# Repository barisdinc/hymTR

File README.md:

# hymTR
APRS Tracker
Arduino Uno ile calisan bir APRS tracker projesidir. 
Temel oalrak asagidaki ozelliklere sahiptir :
- Herhangibir arduino ile calisir
- Telsize hoparlor arayuzunden baglanir
- 4 bitlik bir Direnc iskelesi (resistor ladder) DAC ile calisir (16 seviye)
- Asagidaki verileri GPS den okur
  - Zaman
  - Pozisyon
  - Hiz/yonlenme vb
  - Uydu sayisi
  - Fix durumu
- Smart beacon ozelligi ile hiz ile orantili olarak gonderme sikligini degistirir
- Verileri EEPROM'da saklar
- PC Yazilimi ile tum ayarlari degistirilebilir

Eklenmesi planlanan ozellikler :
- APRS dinleme ozelligi
- Dorji radyolari yonetebilme ozelligi
- Display ekelenebilir

PC Yonetim arayuzu programi "hymTR Ayar Programi" ayri bir repository icindedir.

Donanim detaylari icin <A HREF="https://github.com/barisdinc/hymTR/blob/master/Hardware/README.md">Donanim Sayfasi'na bakabilirsiniz</A>

Ocak 2020

Proje destekcileri :
--------------------
- TA2GY Cem Karagoz
- TA6AEU Emre Keles

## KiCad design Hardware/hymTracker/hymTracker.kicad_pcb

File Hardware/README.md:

hymTRacker Donanim Genel gorunumu

<IMG SRC=https://github.com/barisdinc/hymTR/blob/master/Hardware/pcb_genel.jpeg>
<IMG SRC=https://github.com/barisdinc/hymTR/blob/master/Hardware/pcb_3d_ustten.jpeg>
<IMG SRC=https://github.com/barisdinc/hymTR/blob/master/Hardware/pcb_3d_acili.jpeg>
<IMG SRC=https://github.com/barisdinc/hymTR/blob/master/Hardware/pcb_3d_alttan.jpeg>
<IMG SRC=https://github.com/barisdinc/hymTR/blob/master/Hardware/resim1.jpeg>
<IMG SRC=https://github.com/barisdinc/hymTR/blob/master/Hardware/resim2.jpeg>
<IMG SRC=https://github.com/barisdinc/hymTR/blob/master/Hardware/resim3.jpeg>
<IMG SRC=https://github.com/barisdinc/hymTR/blob/master/Hardware/resim4.jpeg>
<IMG SRC=https://github.com/barisdinc/hymTR/blob/master/Hardware/resim5.jpeg>
<IMG SRC=https://github.com/barisdinc/hymTR/blob/master/Hardware/resim6.jpeg>
<IMG SRC=https://github.com/barisdinc/hymTR/blob/master/Hardware/resim7.jpeg>
<IMG SRC=https://github.com/barisdinc/hymTR/blob/master/Hardware/resim8.jpeg>
<IMG SRC=https://github.com/barisdinc/hymTR/blob/master/Hardware/resim9.jpeg>
<IMG SRC=https://github.com/barisdinc/hymTR/blob/master/Hardware/resim10.jpeg>

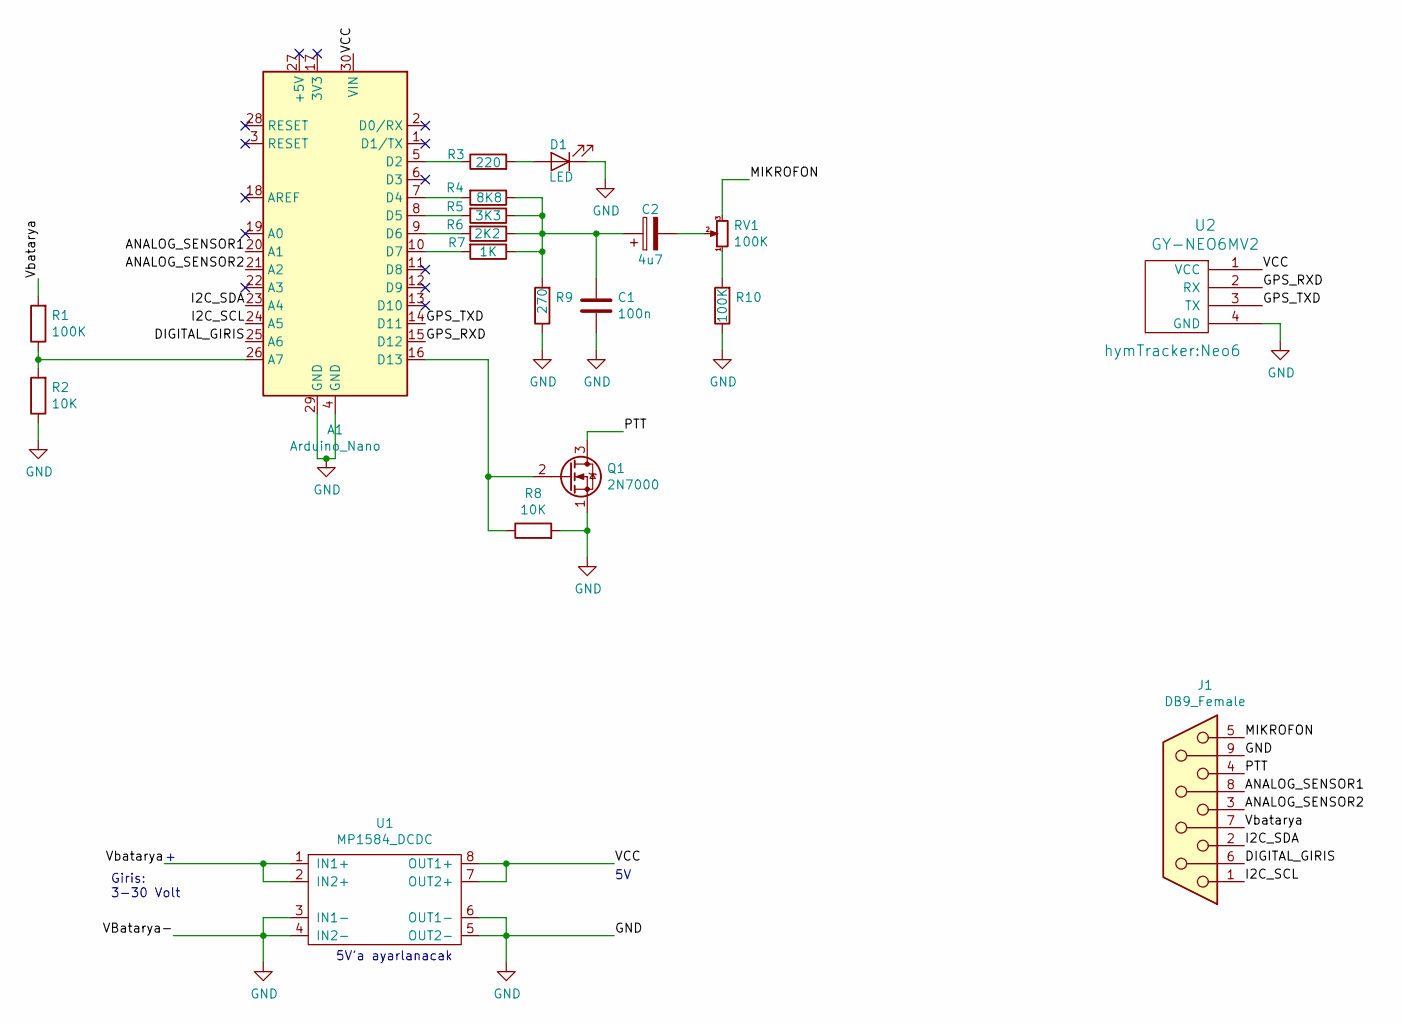
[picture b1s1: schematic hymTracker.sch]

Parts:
A1: Arduino_Nano
C1: 100n; C_0805_2012Metric
C2: 4u7; C_1206_3216Metric
D1: LED; LED_0805_2012Metric
J1: DB9_Female; DSUB-9_Female_Horizontal_P2.77x2.84mm_EdgePinOffset7.70mm_H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
Q1: 2N7000; TO-92_Inline
R1, R10: 100K; R_0805_2012Metric
R2, R8: 10K; R_0805_2012Metric
R3: 220; R_0805_2012Metric
R4: 8K8; R_0805_2012Metric
R5: 3K3; R_0805_2012Metric
R6: 2K2; R_0805_2012Metric
R7: 1K; R_0805_2012Metric
R9: 270; R_0805_2012Metric
RV1: 100K; Potentiometer_ACP_CA9-V10_Vertical_Hole
U1: MP1584_DCDC; MP1854EN_board
U2: GY-NEO6MV2; Neo6

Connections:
/ANALOG_SENSOR1: A1.20 (A1), J1.8
/ANALOG_SENSOR2: A1.21 (A2), J1.3
/DIGITAL_GIRIS: A1.25 (A6), J1.6
/GPS_RXD: A1.15 (D12), U2.2 (RX)
/GPS_TXD: A1.14 (D11), U2.3 (TX)
/I2C_SCL: A1.24 (A5), J1.1
/I2C_SDA: A1.23 (A4), J1.2
/MIKROFON: J1.5, RV1.3
/PTT: J1.4, Q1.3 (D)
/VCC: A1.30 (VIN), U1.7 (OUT2+), U1.8 (OUT1+), U2.1 (VCC)
/Vbatarya: J1.7, R1.2, U1.1 (IN1+), U1.2 (IN2+)
GND: A1.4 (GND), A1.29 (GND), C1.2, D1.1 (K), J1.9, Q1.1 (S), R2.1, R8.2, R9.1, R10.1, U1.3 (IN1-), U1.4 (IN2-), U1.5 (OUT2-), U1.6 (OUT1-), U2.4 (GND)
unnamed: A1.5 (D2), R3.1
unnamed: A1.7 (D4), R4.2
unnamed: A1.8 (D5), R5.2
unnamed: A1.9 (D6), R6.2
unnamed: A1.10 (D7), R7.2
unnamed: A1.16 (D13), Q1.2 (G), R8.1
unnamed: A1.26 (A7), R1.1, R2.2
unnamed: C1.1, C2.1, R4.1, R5.1, R6.1, R7.1, R9.2
unnamed: C2.2, RV1.2
unnamed: D1.2 (A), R3.2
unnamed: R10.2, RV1.1

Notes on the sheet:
5V'a ayarlanacak
Giris: 3-30 Volt

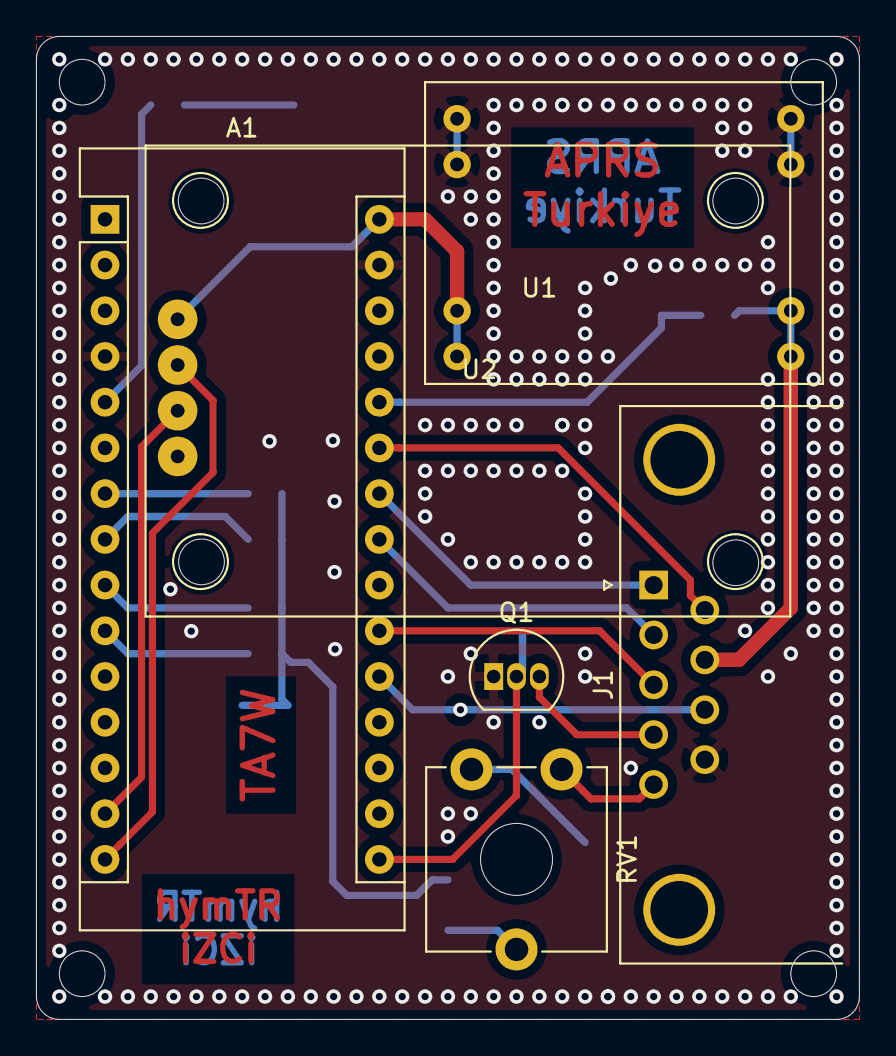
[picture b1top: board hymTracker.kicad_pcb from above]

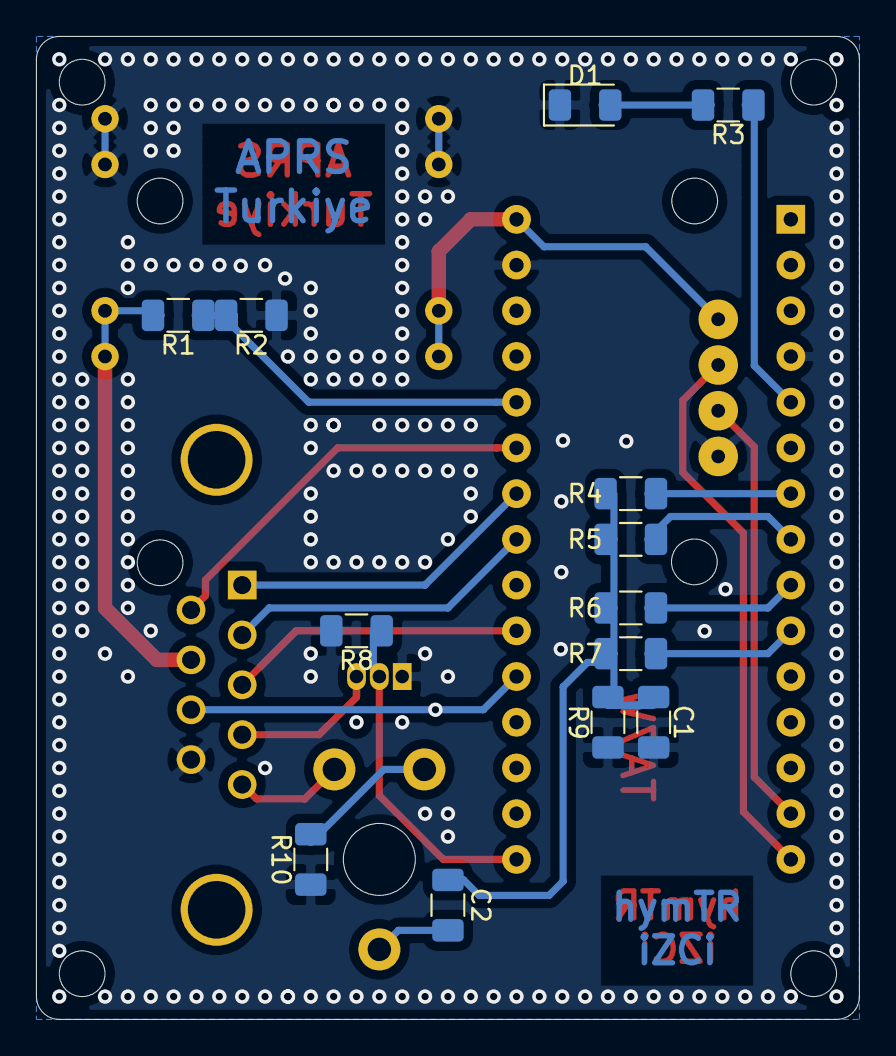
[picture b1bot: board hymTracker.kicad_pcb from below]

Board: 2 copper layers, 45.7 x 54.6 mm, 19 parts (13 on the bottom side), 23 nets.

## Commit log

2020-01-06 ilk baslangic
2020-01-07 initial push
2020-01-10 Seri port atayuzu eklendi.. EEPROM yazma okuma eklendi
2020-01-11 seri port haberlesmesi kabaca tamam
2020-01-11 Adafruit GPS denemesi.. memory yetmiyor
2020-01-18 GPS okuma ve Seri port rutinleri degistirildi
    gps okumak icin nmae NeoGPS kutuphanesine gecildi
    seri port icin neoSWserial kutuphanesi ve interrupt yapisina gecildi
2020-01-18 Seri port yonetim arayuzu
2020-01-19 for backup
2020-01-19 backup 2
2020-01-19 old version
2020-01-19 Derece'den NMEA ya cevirim formulu degistirildi
2020-01-19 aci hesaplari duzeltildi
2020-01-19 altitude feet->metre cevriomi duzeltildi
2020-01-19 modified for new library DIR / SPD/ CSE
2020-01-19 tcommit
2020-01-29 APRS_Destination updated
2020-02-04 last modif for seiral comms
2020-02-05 restructured
2020-02-05 src deleted
2020-02-05 restructure 2
2020-02-05 libraries
2020-02-05 headers
2020-02-05 tests removed
2020-02-05 tested with emre
2020-02-06 sure hatasi
2020-02-09 callsign length problem solved
2020-03-15 Hardware eklendi
2020-03-15 sema cizildi
2020-03-15 pcb ye hazir
2020-03-15 pcb lib
2020-03-16 PCD cizimi tamamlandi
2020-03-16 PCD resimleri
2020-03-16 PCB logo
2020-03-17 yeni 3d elemanlar
2020-03-17 yeni 3d elemanlar 2
2020-03-17 resimler guncellendi
2020-04-17 Panel eklentisi
2020-04-18 panel.. callsign and RULER added
2020-04-18 gerbers created
2020-06-23 basilan
2020-06-23 yedek - kullanma
2020-07-20 re-branding
2020-08-06 dergi yazi (doc)
2020-08-06 dergi yazi (odt)
2020-08-06 dergi yazi (pdf)
2020-08-06 R805->R1206 (small)
2020-08-10 son degisiklikler
2020-08-11 temizlik
2020-08-17 gps ters cevrildi
2020-08-17 gerber output
2020-09-03 dual version
2020-10-02 Destination APIzci duzeltmesi yapildi
2020-10-02 GPS Default var yapildi
2020-10-02 D3 moved to D13 for TX
2020-10-07 cse/head phg corrected
2020-12-21 APRS sembolu gondermeme hatasi duzeltildi
